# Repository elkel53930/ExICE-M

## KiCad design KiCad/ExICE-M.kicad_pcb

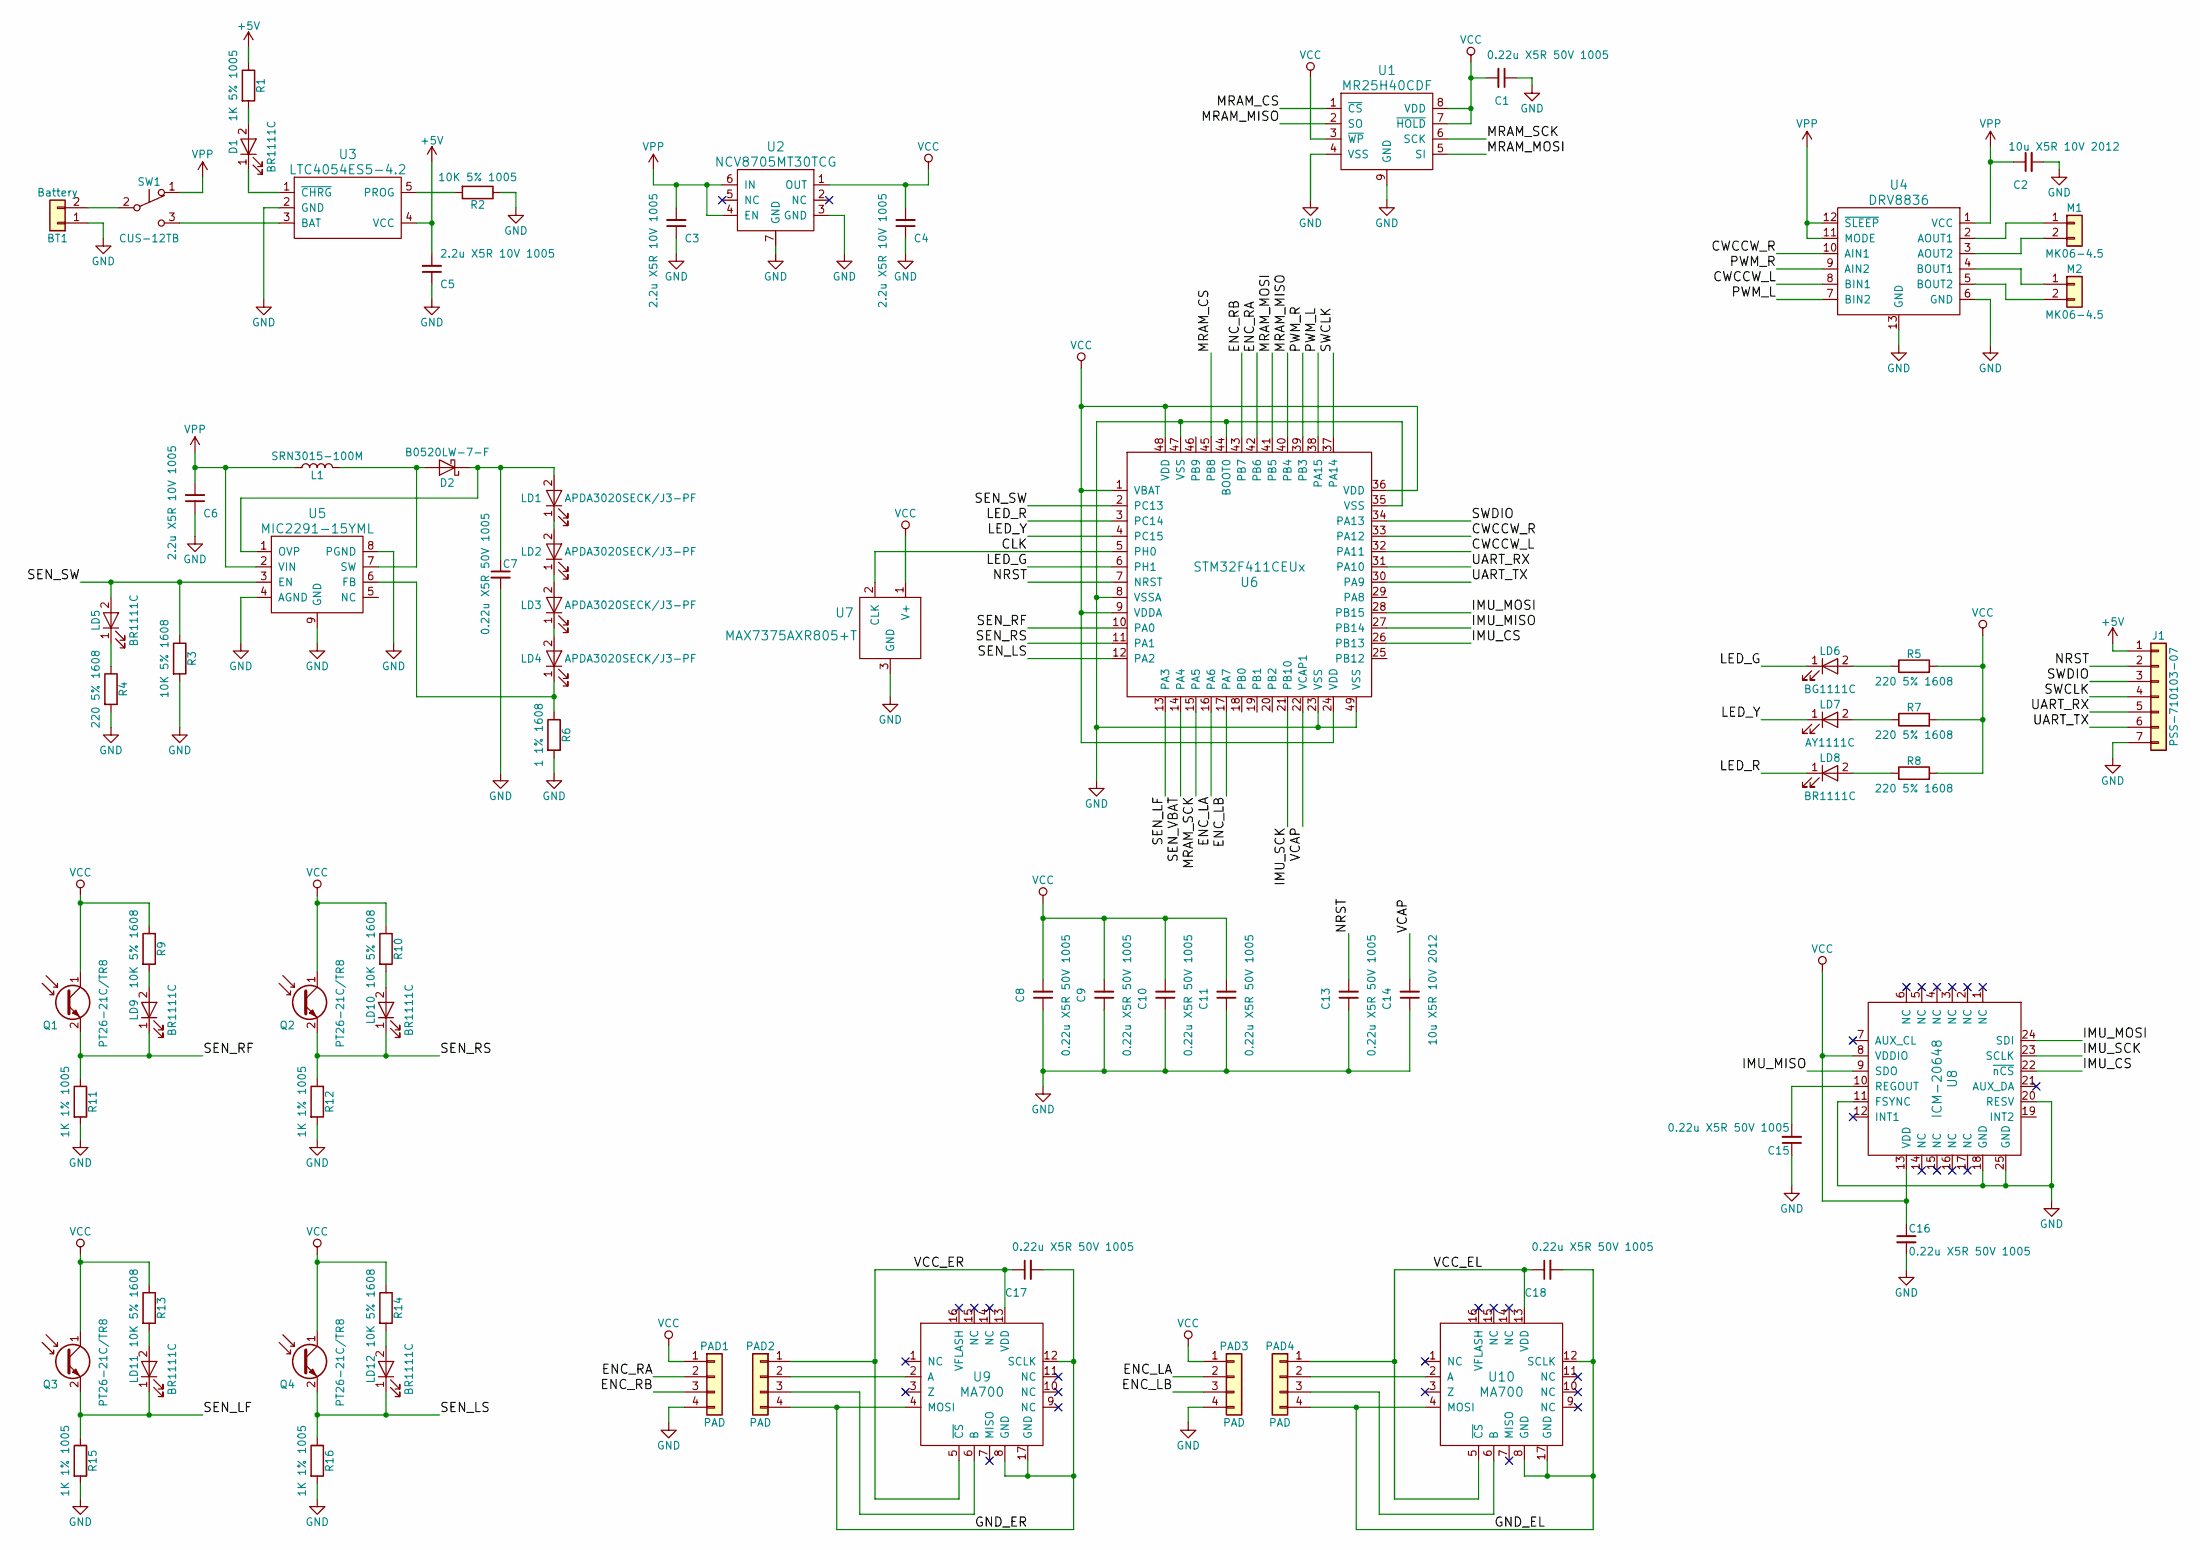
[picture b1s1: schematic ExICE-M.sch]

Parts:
BT1: Battery; B2B-ZR
C1, C7, C8, C9, C10, C11, C13, C15, C16, C17, C18: 0.22u X5R 50V 1005; C_0402
C2, C14: 10u X5R 10V 2012; C_0805
C3, C4, C5, C6: 2.2u X5R 10V 1005; C_0402
D1: BR1111C; LED_0603
D2: B0520LW-7-F; D_SOD-123
J1: PSS-710103-07; 1.27mm_PinHeader_7pole
L1: SRN3015-100M; SRN3015
LD1, LD2, LD3, LD4: APDA3020SECK/J3-PF; APDA3020SECK_J3-PF
LD5, LD8, LD9, LD10, LD11, LD12: BR1111C; LED_0603
LD6: BG1111C; LED_0603
LD7: AY1111C; LED_0603
M1, M2: MK06-4.5
PAD1: PAD; MOTOR_ASSY_R
PAD2, PAD4: PAD; PAD_MAIN-ENC
PAD3: PAD; MOTOR_ASSY_L
Q1, Q2, Q3, Q4: PT26-21C/TR8; PT26-21C_TR8_Right
R1: 1K 5% 1005; R_0402
R2: 10K 5% 1005; R_0402
R3, R9, R10, R13, R14: 10K 5% 1608; R_0603
R4, R5, R7, R8: 220 5% 1608; R_0603
R6: 1 1% 1608; R_0603
R11, R12, R15, R16: 1K 1% 1005; R_0402
SW1: CUS-12TB
U1: MR25H40CDF; DFN8_Small_Flag
U2: NCV8705MT30TCG; DFN-6-1EP_2x2mm_Pitch0.65mm
U3: LTC4054ES5-4.2; SOT-23-5
U4: DRV8836; WSON-12-1EP_3x2mm_Pitch0.5mm
U5: MIC2291-15YML; 8PinMLF
U6: STM32F411CEUx; QFN-48-1EP_7x7mm_Pitch0.5mm
U7: MAX7375AXR805+T; SOT-323_SC-70
U8: ICM-20648; QFN-24-1EP_3x3mm_Pitch0.4mm
U9, U10: MA700; QFN-16-1EP_3x3mm_Pitch0.5mm

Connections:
+5V: C5.2, J1.1, R1.1, U3.4 (VCC)
/CLK: U6.5 (PH0), U7.2 (CLK)
/CWCCW_L: U4.8 (BIN1), U6.32 (PA11)
/CWCCW_R: U4.10 (AIN1), U6.33 (PA12)
/ENC_LA: PAD3.2, U6.16 (PA6)
/ENC_LB: PAD3.3, U6.17 (PA7)
/ENC_RA: PAD1.2, U6.42 (PB6)
/ENC_RB: PAD1.3, U6.43 (PB7)
/GND_EL: C18.2, PAD4.4, U10.4 (MOSI), U10.8 (GND), U10.12 (SCLK), U10.17 (GND)
/GND_ER: C17.2, PAD2.4, U9.4 (MOSI), U9.8 (GND), U9.12 (SCLK), U9.17 (GND)
/IMU_CS: U6.26 (PB13), U8.22 (~nCS)
/IMU_MISO: U6.27 (PB14), U8.9 (SDO)
/IMU_MOSI: U6.28 (PB15), U8.24 (SDI)
/IMU_SCK: U6.21 (PB10), U8.23 (SCLK)
/LED_G: LD6.1 (K), U6.6 (PH1)
/LED_R: LD8.1 (K), U6.3 (PC14)
/LED_Y: LD7.1 (K), U6.4 (PC15)
/MRAM_CS: U1.1 (~CS), U6.45 (PB8)
/MRAM_MISO: U1.2 (SO), U6.40 (PB4)
/MRAM_MOSI: U1.5 (SI), U6.41 (PB5)
/MRAM_SCK: U1.6 (SCK), U6.15 (PA5)
/NRST: C13.2, J1.2, U6.7 (NRST)
/PWM_L: U4.7 (BIN2), U6.38 (PA15)
/PWM_R: U4.9 (AIN2), U6.39 (PB3)
/SEN_LF: LD11.1 (K), Q3.2 (E), R15.1, U6.13 (PA3)
/SEN_LS: LD12.1 (K), Q4.2 (E), R16.1, U6.12 (PA2)
/SEN_RF: LD9.1 (K), Q1.2 (E), R11.1, U6.10 (PA0)
/SEN_RS: LD10.1 (K), Q2.2 (E), R12.1, U6.11 (PA1)
/SEN_SW: LD5.2 (A), R3.1, U5.3 (EN), U6.2 (PC13)
/SWCLK: J1.4, U6.37 (PA14)
/SWDIO: J1.3, U6.34 (PA13)
/UART_RX: J1.5, U6.31 (PA10)
/UART_TX: J1.6, U6.30 (PA9)
/VCAP: C14.2, U6.22 (VCAP1)
/VCC_EL: C18.1, PAD4.1, U10.5 (~CS), U10.13 (VDD)
/VCC_ER: C17.1, PAD2.1, U9.5 (~CS), U9.13 (VDD)
GND: BT1.1, C1.1, C2.2, C3.1, C4.1, C5.1, C6.1, C7.2, C8.1, C9.1, C10.1, C11.1, C13.1, C14.1, C15.1, C16.2, J1.7, PAD1.4, PAD3.4, R2.1, R3.2, R4.2, R6.2, R11.2, R12.2, R15.2, R16.2, U1.4 (VSS), U1.9 (GND), U2.3 (GND), U2.7 (GND), U3.2 (GND), U4.6 (GND), U4.13 (GND), U5.4 (AGND), U5.8 (PGND), U5.9 (GND), U6.8 (VSSA), U6.23 (VSS), U6.35 (VSS), U6.44 (BOOT0), U6.47 (VSS), U6.49 (VSS), U7.3 (GND), U8.11 (FSYNC), U8.18 (GND), U8.20 (RESV), U8.25 (GND)
unnamed: BT1.2, SW1.2 (B)
unnamed: C7.1, D2.1 (K), LD1.2 (A), U5.1 (OVP)
unnamed: C15.2, U8.10 (REGOUT)
unnamed: D1.1 (K), U3.1 (~CHRG)
unnamed: D1.2 (A), R1.2
unnamed: D2.2 (A), L1.2, U5.7 (SW)
unnamed: LD1.1 (K), LD2.2 (A)
unnamed: LD2.1 (K), LD3.2 (A)
unnamed: LD3.1 (K), LD4.2 (A)
unnamed: LD4.1 (K), R6.1, U5.6 (FB)
unnamed: LD5.1 (K), R4.1
unnamed: LD6.2 (A), R5.1
unnamed: LD7.2 (A), R7.1
unnamed: LD8.2 (A), R8.1
unnamed: LD9.2 (A), R9.2
unnamed: LD10.2 (A), R10.2
unnamed: LD11.2 (A), R13.2
unnamed: LD12.2 (A), R14.2
unnamed: M1.1, U4.2 (AOUT1)
unnamed: M1.2, U4.3 (AOUT2)
unnamed: M2.1, U4.4 (BOUT1)
unnamed: M2.2, U4.5 (BOUT2)
unnamed: PAD2.2, U9.2 (A)
unnamed: PAD2.3, U9.6 (B)
unnamed: PAD4.2, U10.2 (A)
unnamed: PAD4.3, U10.6 (B)
unnamed: R2.2, U3.5 (PROG)
unnamed: SW1.3 (C), U3.3 (BAT)
VCC: C1.2, C4.2, C8.2, C9.2, C10.2, C11.2, C16.1, PAD1.1, PAD3.1, Q1.1 (C), Q2.1 (C), Q3.1 (C), Q4.1 (C), R5.2, R7.2, R8.2, R9.1, R10.1, R13.1, R14.1, U1.3 (~WP), U1.7 (~HOLD), U1.8 (VDD), U2.1 (OUT), U6.1 (VBAT), U6.9 (VDDA), U6.24 (VDD), U6.36 (VDD), U6.48 (VDD), U7.1 (V+), U8.8 (VDDIO), U8.13 (VDD)
VPP: C2.1, C3.2, C6.2, L1.1, SW1.1 (A), U2.4 (EN), U2.6 (IN), U4.1 (VCC), U4.11 (MODE), U4.12 (~SLEEP), U5.2 (VIN)

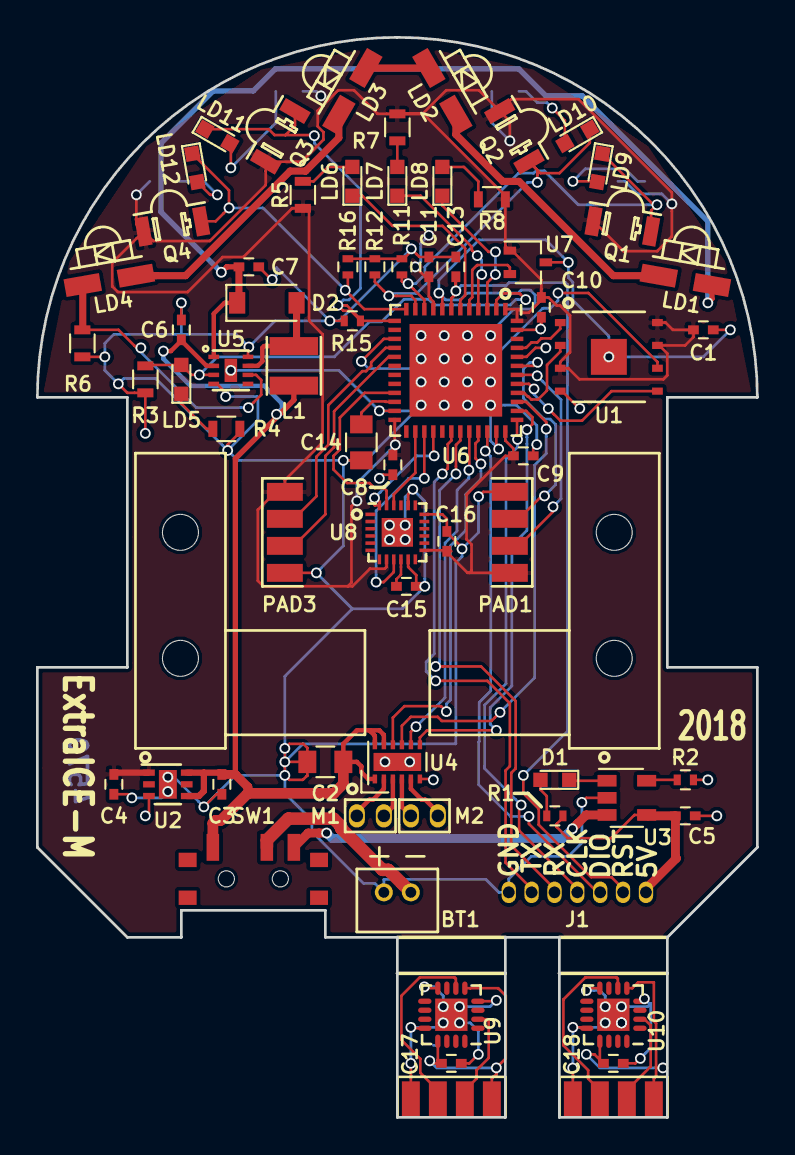
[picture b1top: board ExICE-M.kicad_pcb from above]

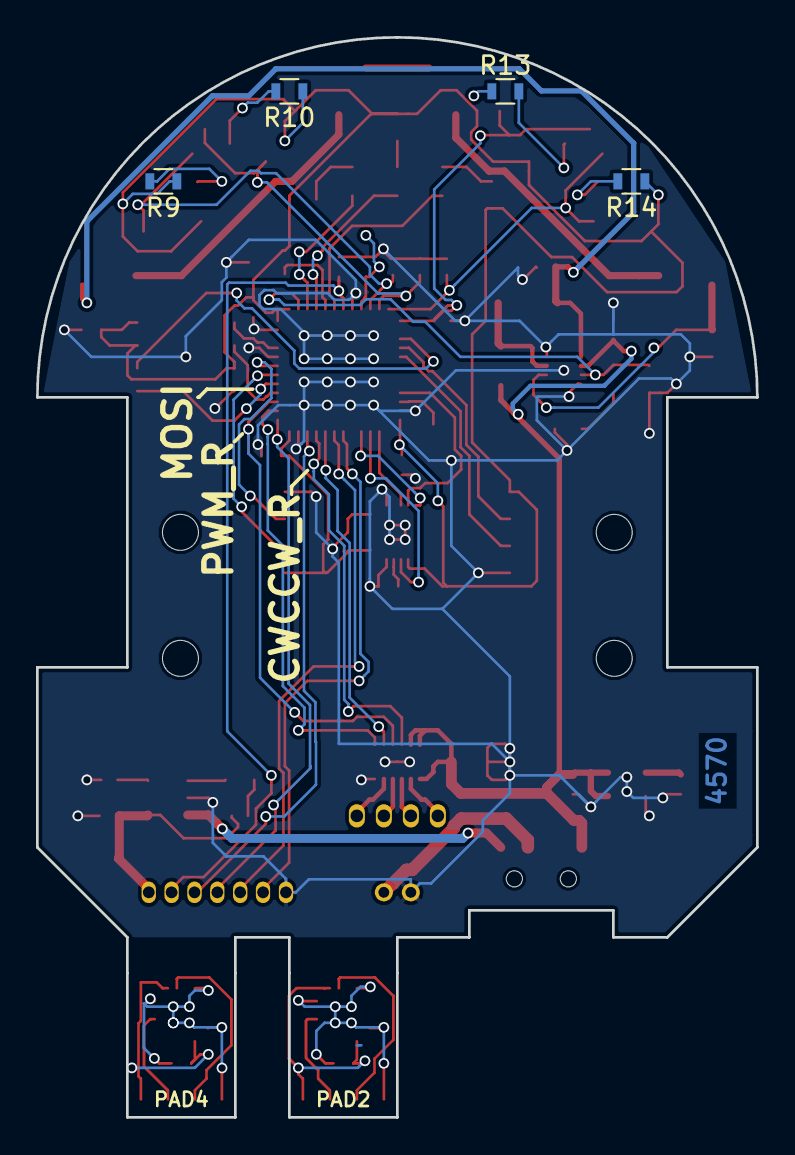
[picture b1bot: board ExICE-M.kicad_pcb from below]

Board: 2 copper layers, 40.0 x 60.0 mm, 71 parts (4 on the bottom side), 67 nets.

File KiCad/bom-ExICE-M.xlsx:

Reference | Manufacturer | Value | Note
BT1 | JST | B2B-ZR
C1 |  | 0.22u X5R 50V 1005
C10 |  | 0.22u X5R 50V 1005
C11 |  | 0.22u X5R 50V 1005
C13 |  | 0.22u X5R 50V 1005
C14 |  | 10u X5R 10V 2012
C15 |  | 0.22u X5R 50V 1005
C16 |  | 0.22u X5R 50V 1005
C17 |  | 0.22u X5R 50V 1005
C18 |  | 0.22u X5R 50V 1005
C2 |  | 10u X5R 10V 2012
C3 |  | 2.2u X5R 10V 1005
C4 |  | 2.2u X5R 10V 1005
C5 |  | 2.2u X5R 10V 1005
C6 |  | 2.2u X5R 10V 1005
C7 |  | 0.22u X5R 50V 1005
C8 |  | 0.22u X5R 50V 1005
C9 |  | 0.22u X5R 50V 1005
D1 | Stanley Electronic | BR1111C
D2 | Diodes | B0520LW-7-F
L1 | Bourns | SRN3015-100M
LD1 | Kingbright | APDA3020SECK/J3-PF
LD10 | Stanley Electronic | BR1111C
LD11 | Stanley Electronic | BR1111C
LD12 | Stanley Electronic | BR1111C
LD2 | Kingbright | APDA3020SECK/J3-PF
LD3 | Kingbright | APDA3020SECK/J3-PF
LD4 | Kingbright | APDA3020SECK/J3-PF
LD5 | Stanley Electronic | BR1111C
LD6 | Stanley Electronic | BG1111C
LD7 | Stanley Electronic | AY1111C
LD8 | Stanley Electronic | BR1111C
LD9 | Stanley Electronic | BR1111C
R1 |  | 1K 5% 1005
R11 |  | 1K 1% 1005
R12 |  | 1K 1% 1005
R15 |  | 1K 1% 1005
R16 |  | 1K 1% 1005
R2 |  | 10K 5% 1005
R3 |  | 10K 5% 1608
R4 |  | 220 5% 1608
R5 |  | 220 5% 1608
R6 |  | 1 1% 1608
R7 |  | 220 5% 1608
R8 |  | 220 5% 1608
SW1 | Nidec Copal | CUS-12TB
U1 | Everspin | MR25H40CDF
U10 | Monolithic Power Systems | MA700
U2 | On Semiconductor | NCV8705MT30TCG
U3 | Linear Technology | LTC4054ES5-4.2
U4 | Texas Instruments | DRV8836DSSR
U5 | Microchip Technology | MIC2291-15YML
U6 | STMicroelectronics | STM32F411CEU6
U7 | Maxim | MAX7375AXR805+T
U8 | TDK InvenSense | ICM-20648
U9 | Monolithic Power Systems | MA700
J1 |  |  | Not mount
R10 |  |  | Not mount
R13 |  |  | Not mount
R14 |  |  | Not mount
R9 |  |  | Not mount
PAD1 |  |  | Not mount
PAD2 |  |  | Not mount
PAD3 |  |  | Not mount
PAD4 |  |  | Not mount
M1 |  |  | Not mount
M2 |  |  | Not mount
Q1 |  |  | Not mount
Q2 |  |  | Not mount
Q3 |  |  | Not mount
Q4 |  |  | Not mount

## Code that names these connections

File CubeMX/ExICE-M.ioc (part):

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Mcu.Name=STM32F411C(C-E)Ux
Mcu.Package=UFQFPN48
Mcu.UserName=STM32F411CEUx
PA0-WKUP.Signal=ADCx_IN0
PA1.Signal=ADCx_IN1
PA10.Mode=Asynchronous
PA10.Signal=USART1_RX
PA13.Mode=Serial_Wire
PA13.Signal=SYS_JTMS-SWDIO
PA14.Mode=Serial_Wire
PA14.Signal=SYS_JTCK-SWCLK
PA15.Signal=S_TIM2_CH1_ETR
PA2.Signal=ADCx_IN2
PA3.Signal=ADCx_IN3
PA4.Signal=ADCx_IN4
PA5.Mode=Full_Duplex_Master
PA5.Signal=SPI1_SCK
PA6.Signal=S_TIM3_CH1
PA7.Signal=S_TIM3_CH2
PA9.Mode=Asynchronous
PA9.Signal=USART1_TX
PB10.Mode=Full_Duplex_Master
PB10.Signal=SPI2_SCK
PB14.Mode=Full_Duplex_Master
PB14.Signal=SPI2_MISO
PB15.Mode=Full_Duplex_Master
PB15.Signal=SPI2_MOSI
PB3.Signal=S_TIM2_CH2
PB4.Mode=Full_Duplex_Master
PB4.Signal=SPI1_MISO
PB5.Mode=Full_Duplex_Master
PB5.Signal=SPI1_MOSI
PB6.Signal=S_TIM4_CH1
PB7.Signal=S_TIM4_CH2
RCC.HSE_VALUE=25000000
RCC.SYSCLKFreq_VALUE=72000000
RCC.SYSCLKSource=RCC_SYSCLKSOURCE_PLLCLK
board=custom

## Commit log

2018-11-22 add readme
2018-11-25 Add schematic(PDF).
2019-12-02 KiCadバージョンアップ
